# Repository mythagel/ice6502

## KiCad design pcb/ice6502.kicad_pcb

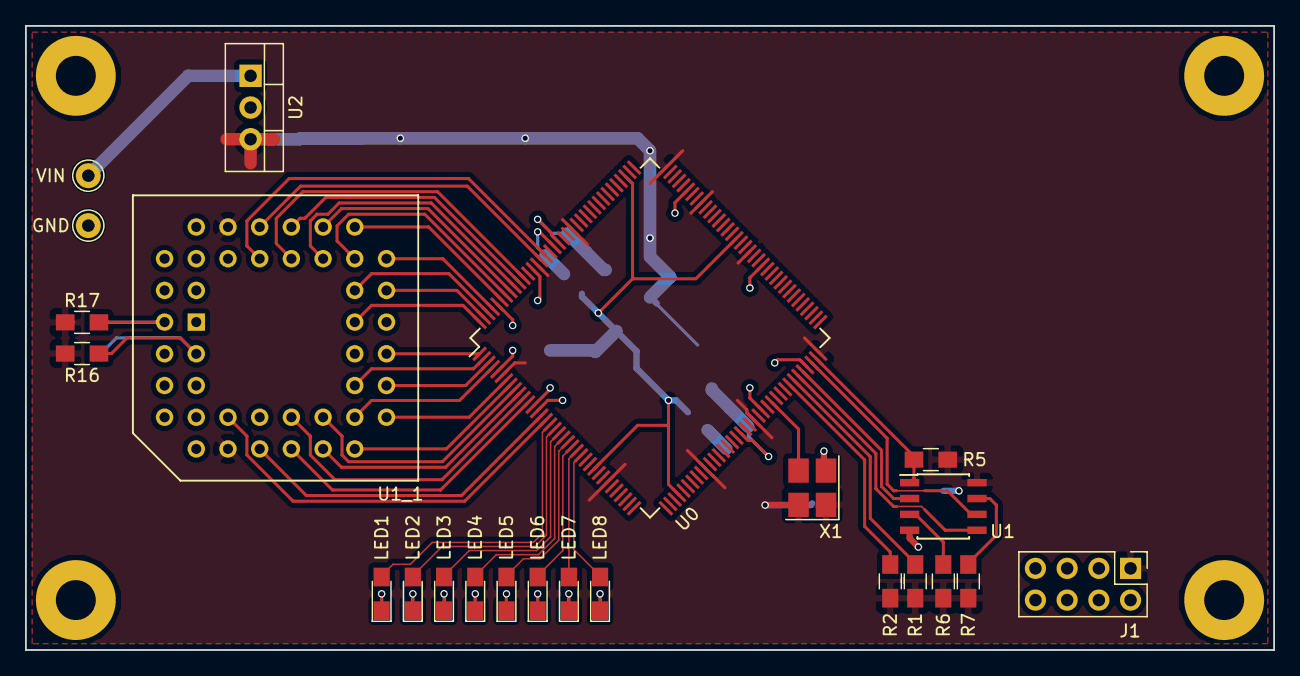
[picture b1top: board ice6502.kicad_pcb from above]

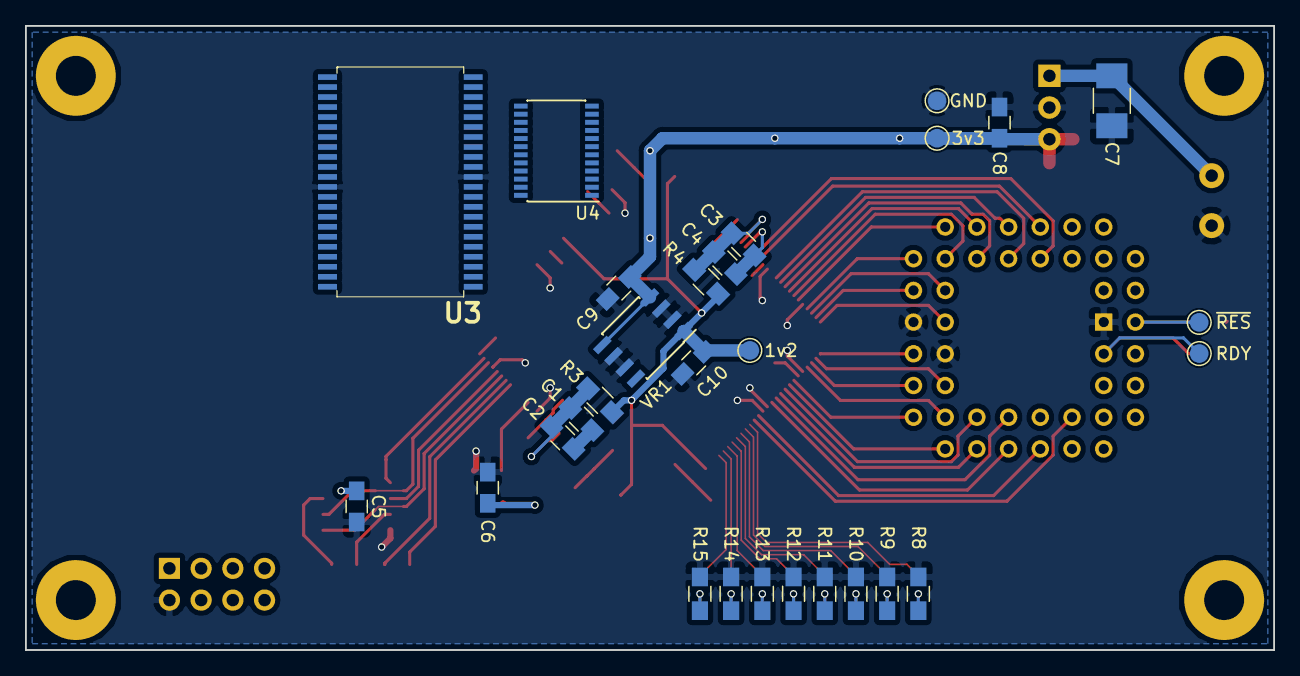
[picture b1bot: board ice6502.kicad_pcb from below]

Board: 2 copper layers, 100.0 x 50.0 mm, 51 parts (28 on the bottom side), 93 nets.

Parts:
C1, C3: 10uF; C_0805_HandSoldering
C2, C4, C5: 100nF; C_0805_HandSoldering
C6: 10nF; C_0805_HandSoldering
C7: 10uF/50V; C_1210_HandSoldering
C8: 22uF/10V; C_0805_HandSoldering
C9, C10: 1uF; C_0805_HandSoldering
J1: Programming Header; Pin_Header_Straight_2x04_Pitch2.54mm
J2: RDY; Test_Point_Pad_d1.5mm
J3: ~RES; Test_Point_Pad_d1.5mm
J4: VIN; Pin_d1.0mm_L10.0mm
J5: GND; Pin_d1.0mm_L10.0mm
J6: 3v3; Test_Point_Pad_d1.5mm
J7: 1v2; Test_Point_Pad_d1.5mm
J8: GND; Test_Point_Pad_d1.5mm
LED1, LED2, LED3, LED4, LED5, LED6, LED7, LED8: LED; LED_0805_HandSoldering
R1, R5, R6, R7: 10KOhm; R_0805_HandSoldering
R2, R8, R9, R10, R11, R12, R13, R14, R15, R17: 2.2KOhm; R_0805_HandSoldering
R3, R4: 100Ohm; R_0805_HandSoldering
R16: 3.3KOhm; R_0805_HandSoldering
U0: iCE40-HX4K-TQ144; TQFP-144_20x20mm_Pitch0.5mm
U1: AT25SF041-SSHD-B; SOIC-8_3.9x4.9mm_Pitch1.27mm
U1_1: W65C816S_PLCC; PLCC44
U2: VXO7803-1000; TO-220_Vertical
U3: IS61WV5128EDBLL-10TLI; TSOP-II-44_10.16x18.42_Pitch0.8mm
U4: STP16CP05; TSSOP-24_4.4x7.8mm_Pitch0.65mm
VR1: LDL112D12R; SOIC-8_3.9x4.9mm_Pitch1.27mm
X1: ASE-xxxMHz; Oscillator_SMD_Abracon_ASE-4pin_3.2x2.5mm_HandSoldering

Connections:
1v2: C10.1, J7.1, R3.1, R4.1, U0.27, U0.40, U0.92, U0.111, VR1.1
3v3: C5.1, C6.1, C8.1, C9.1, J1.1, J6.1, R1.1, R2.1, R5.1, R6.1, R7.1, R16.1, R17.1, U0.6, U0.30, U0.46, U0.57, U0.72, U0.89, U0.100, U0.108, U0.123, U0.131, U1.8, U1_1.9, U1_1.37, U2.3, U3.11, U3.33, VR1.4, VR1.5, X1.1, X1.4
CDONE: J1.3, R2.2, U0.65
CS: J1.8, R5.2, U0.71, U1.1
GND: C5.2, C6.2, C7.2, C8.2, C9.2, C10.2, J1.2, J5.1, J8.1, R8.2, R9.2, R10.2, R11.2, R12.2, R13.2, R14.2, R15.2, U0.5, U0.13, U0.14, U0.59, U0.69, U0.86, U0.103, U0.132, U0.140, U1.4, U1_1.1, U1_1.23, U1_1.24, U2.2, U3.12, U3.34, VR1.2, VR1.3, VR1.6, VR1.7, X1.2
MISO: J1.6, U0.68, U1.2
MOSI: J1.5, U0.67, U1.5
unnamed: U0.61, X1.3
unnamed: LED1.2, U0.17
unnamed: LED1.1, R8.1
unnamed: LED2.2, U0.18
unnamed: LED2.1, R9.1
unnamed: LED3.2, U0.19
unnamed: LED3.1, R10.1
unnamed: LED4.2, U0.20
unnamed: LED4.1, R11.1
unnamed: LED5.2, U0.21
unnamed: LED5.1, R12.1
unnamed: LED6.2, U0.22
unnamed: LED6.1, R13.1
unnamed: LED7.2, U0.23
unnamed: LED7.1, R14.1
unnamed: LED8.2, U0.24
unnamed: LED8.1, R15.1
unnamed: U0.37, U3.8
unnamed: U0.38, U3.15
unnamed: U0.39, U3.37
PLLGND: C1.2, C2.2, U0.53
PLLGND_1: C3.2, C4.2, U0.127
PLLVCC: C1.1, C2.1, R3.2, U0.54
PLLVCC_1: C3.1, C4.1, R4.2, U0.126
RDY: J2.1, R16.2, U1_1.3
SCK: J1.7, U0.70, U1.6
VDA: U0.128, U1_1.43
VIN: C7.1, J4.1, U2.1
VPA: U0.33, U1_1.8
addr_b0: U0.73, U3.3
addr_b1: U0.74, U3.4
addr_b2: U0.75, U3.5
addr_b3: U0.76, U3.6
addr_b4: U0.78, U3.7
addr_b5: U0.79, U3.16
addr_b6: U0.80, U3.17
addr_b7: U0.81, U3.18
addr_b8: U0.82, U3.19
addr_b9: U0.83, U3.20
addr_b10: U0.84, U3.26
addr_b11: U0.85, U3.27
addr_b12: U0.87, U3.28
addr_b13: U0.88, U3.29
addr_b14: U0.90, U3.30
addr_b15: U0.91, U3.38
addr_b16: U0.93, U3.39
addr_b17: U0.94, U3.40
addr_b18: U0.95, U3.41
addr_c0: U0.16, U1_1.10
addr_c1: U0.15, U1_1.11
addr_c2: U0.12, U1_1.13
addr_c3: U0.11, U1_1.14
addr_c4: U0.10, U1_1.15
addr_c5: U0.9, U1_1.16
addr_c6: U0.8, U1_1.17
addr_c7: U0.7, U1_1.18
addr_c8: U0.4, U1_1.19
addr_c9: U0.3, U1_1.20
addr_c10: U0.2, U1_1.21
addr_c11: U0.1, U1_1.22
addr_c12: U0.144, U1_1.25
addr_c13: U0.143, U1_1.26
addr_c14: U0.142, U1_1.27
addr_c15: U0.141, U1_1.28
data0: U0.96, U3.9
data1: U0.97, U3.10
data2: U0.98, U3.13
data3: U0.99, U3.14
data4: U0.101, U3.31
data5: U0.102, U3.32
data6: U0.104, U3.35
data7: U0.105, U3.36
data_c0: U0.129, U1_1.36
data_c1: U0.130, U1_1.35
data_c2: U0.134, U1_1.34
data_c3: U0.135, U1_1.33
data_c4: U0.136, U1_1.32
data_c5: U0.137, U1_1.31
data_c6: U0.138, U1_1.30
data_c7: U0.139, U1_1.29
~ABORT: U0.32, U1_1.4
~CRESET: J1.4, R1.2, U0.66
~HOLD: R7.2, U1.7
~RES: J3.1, R17.2, U1_1.44
~VP: U0.34, U1_1.2
~WP: R6.2, U1.3

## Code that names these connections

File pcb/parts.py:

#!/usr/bin/python3
from skidl import *

# local parts
local = SchLib(name='local')

led = Part(name='LED', tool=SKIDL, dest=TEMPLATE)
led.ref_prefix = 'LED'
led.description = 'Generic LED'
led += Pin(num=1, name='1', func=Pin.PASSIVE)
led += Pin(num=2, name='2', func=Pin.PASSIVE)
local += led

# LD112 linear regulator
ldl112 = Part(name='LDL112_SO8', tool=SKIDL, dest=TEMPLATE)
ldl112.ref_prefix = 'VR'
ldl112.description = '1.2 A low quiescent current LDO'
ldl112 += Pin(num=1, name='VOUT', func=Pin.PWROUT)
ldl112 += Pin(num=2, name='GND', func=Pin.PWRIN)
ldl112 += Pin(num=3, name='GND', func=Pin.PWRIN)
ldl112 += Pin(num=4, name='VIN', func=Pin.PWRIN)
ldl112 += Pin(num=5, name='EN', func=Pin.INPUT)
ldl112 += Pin(num=6, name='GND', func=Pin.PWRIN)
ldl112 += Pin(num=7, name='GND', func=Pin.PWRIN)
ldl112 += Pin(num=8, name='NC', func=Pin.NOCONNECT)
local += ldl112

W65C816S = Part(name='W65C816S_PLCC', tool=SKIDL, dest=TEMPLATE)
W65C816S.ref_prefix = 'U'
W65C816S.description = 'W65C816S 8/16–bit Microprocessor'
W65C816S += Pin(num='1', name='VSS', func=Pin.PWRIN)
W65C816S += Pin(num='2', name='VPB', func=Pin.OUTPUT)
W65C816S += Pin(num='3', name='RDY', func=Pin.BIDIR)
W65C816S += Pin(num='4', name='ABORTB', func=Pin.INPUT)
W65C816S += Pin(num='5', name='IRQB', func=Pin.INPUT)
W65C816S += Pin(num='6', name='MLB', func=Pin.OUTPUT)
W65C816S += Pin(num='7', name='NMIB', func=Pin.INPUT)
W65C816S += Pin(num='8', name='VPA', func=Pin.OUTPUT)
W65C816S += Pin(num='9', name='VDD', func=Pin.PWRIN)
W65C816S += Pin(num='10', name='A0', func=Pin.OUTPUT)
W65C816S += Pin(num='11', name='A1', func=Pin.OUTPUT)
W65C816S += Pin(num='12', name='NC', func=Pin.NOCONNECT)
W65C816S += Pin(num='13', name='A2', func=Pin.OUTPUT)
W65C816S += Pin(num='14', name='A3', func=Pin.OUTPUT)
W65C816S += Pin(num='15', name='A4', func=Pin.OUTPUT)
W65C816S += Pin(num='16', name='A5', func=Pin.OUTPUT)
W65C816S += Pin(num='17', name='A6', func=Pin.OUTPUT)
W65C816S += Pin(num='18', name='A7', func=Pin.OUTPUT)
W65C816S += Pin(num='19', name='A8', func=Pin.OUTPUT)
W65C816S += Pin(num='20', name='A9', func=Pin.OUTPUT)
W65C816S += Pin(num='21', name='A10', func=Pin.OUTPUT)
W65C816S += Pin(num='22', name='A11', func=Pin.OUTPUT)
W65C816S += Pin(num='23', name='VSS', func=Pin.PWRIN)
W65C816S += Pin(num='24', name='VSS', func=Pin.PWRIN)
W65C816S += Pin(num='25', name='A12', func=Pin.OUTPUT)
W65C816S += Pin(num='26', name='A13', func=Pin.OUTPUT)
W65C816S += Pin(num='27', name='A14', func=Pin.OUTPUT)
W65C816S += Pin(num='28', name='A15', func=Pin.OUTPUT)
W65C816S += Pin(num='29', name='D7', func=Pin.TRISTATE)
W65C816S += Pin(num='30', name='D6', func=Pin.TRISTATE)
W65C816S += Pin(num='31', name='D5', func=Pin.TRISTATE)
W65C816S += Pin(num='32', name='D4', func=Pin.TRISTATE)
W65C816S += Pin(num='33', name='D3', func=Pin.TRISTATE)
W65C816S += Pin(num='34', name='D2', func=Pin.TRISTATE)
W65C816S += Pin(num='35', name='D1', func=Pin.TRISTATE)
W65C816S += Pin(num='36', name='D0', func=Pin.TRISTATE)
W65C816S += Pin(num='37', name='VDD', func=Pin.PWRIN)
W65C816S += Pin(num='38', name='RWB', func=Pin.OUTPUT)
W65C816S += Pin(num='39', name='E', func=Pin.OUTPUT)
W65C816S += Pin(num='40', name='BE', func=Pin.INPUT)
W65C816S += Pin(num='41', name='PHI2', func=Pin.INPUT)
W65C816S += Pin(num='42', name='MX', func=Pin.OUTPUT)
W65C816S += Pin(num='43', name='VDA', func=Pin.OUTPUT)
W65C816S += Pin(num='44', name='RESB', func=Pin.INPUT)
local += W65C816S

# LED Driver
stp16 = Part(name='STP16CP05', tool=SKIDL, dest=TEMPLATE)
stp16.ref_prefix = 'U'
stp16.description = '16-bit constant current LED sink driver'
stp16 += Pin(num=1, name='GND', func=Pin.PWRIN)
stp16 += Pin(num=2, name='SDI', func=Pin.INPUT)
stp16 += Pin(num=3, name='CLK', func=Pin.INPUT)
stp16 += Pin(num=4, name='LE', func=Pin.INPUT)
stp16 += Pin(num=5, name='OUT0', func=Pin.PWROUT)
stp16 += Pin(num=6, name='OUT1', func=Pin.PWROUT)
stp16 += Pin(num=7, name='OUT2', func=Pin.PWROUT)
stp16 += Pin(num=8, name='OUT3', func=Pin.PWROUT)
stp16 += Pin(num=9, name='OUT4', func=Pin.PWROUT)
stp16 += Pin(num=10, name='OUT5', func=Pin.PWROUT)
stp16 += Pin(num=11, name='OUT6', func=Pin.PWROUT)
stp16 += Pin(num=12, name='OUT7', func=Pin.PWROUT)
stp16 += Pin(num=13, name='OUT8', func=Pin.PWROUT)
stp16 += Pin(num=14, name='OUT9', func=Pin.PWROUT)
stp16 += Pin(num=15, name='OUT10', func=Pin.PWROUT)
stp16 += Pin(num=16, name='OUT11', func=Pin.PWROUT)
stp16 += Pin(num=17, name='OUT12', func=Pin.PWROUT)
stp16 += Pin(num=18, name='OUT13', func=Pin.PWROUT)
stp16 += Pin(num=19, name='OUT14', func=Pin.PWROUT)
stp16 += Pin(num=20, name='OUT15', func=Pin.PWROUT)
stp16 += Pin(num=21, name='~OE', func=Pin.INPUT)
stp16 += Pin(num=22, name='SDO', func=Pin.OUTPUT)
stp16 += Pin(num=23, name='R-EXT', func=Pin.INPUT)
stp16 += Pin(num=24, name='Vdd', func=Pin.PWRIN)
local += stp16

is62wvs = Part(name='IS62WVS_SOIC', tool=SKIDL, dest=TEMPLATE)
is62wvs.ref_prefix = 'U'
is62wvs.description = 'Fast serial SRAM'
is62wvs += Pin(num=1, name='~CS', func=Pin.INPUT)
is62wvs += Pin(num=2, name='SIO1', func=Pin.BIDIR)
is62wvs += Pin(num=3, name='SIO2', func=Pin.BIDIR)
is62wvs += Pin(num=4, name='VSS', func=Pin.PWRIN)
is62wvs += Pin(num=5, name='SIO0', func=Pin.BIDIR)
is62wvs += Pin(num=6, name='SCK', func=Pin.INPUT)
is62wvs += Pin(num=7, name='SIO3', func=Pin.BIDIR)
is62wvs += Pin(num=8, name='VDD', func=Pin.PWRIN)
local += is62wvs

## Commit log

2018-06-09 Initial
2018-06-09 wip2
2018-06-10 wip3
2018-06-10 jkjsdf
2018-06-13 More datasheets and route power
2018-06-14 Tidy bus setup
2018-06-18 Move to pcb dir
2018-06-23 filter out passives
2018-06-23 Playing with pcb layout
2018-06-24 learning...
2018-06-28 Playing with pcbnew
2018-06-29 Cleanup led & 3v3 pour on top layer
2018-06-29 Cleanup pcb & start naming nets
2018-06-30 Align more components on grid
2018-06-30 Tidying pcb
2018-06-30 Continue on pcb
2018-07-01 Last commit for this revision
2018-07-03 Import skidl
2018-07-03 Use modified skidl
    Enforce manual references to ensure stability when reordering parts.
2018-07-04 Assigned references
